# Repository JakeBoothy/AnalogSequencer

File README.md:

# SoundLabSequencer
A eurorack analog sequencer.

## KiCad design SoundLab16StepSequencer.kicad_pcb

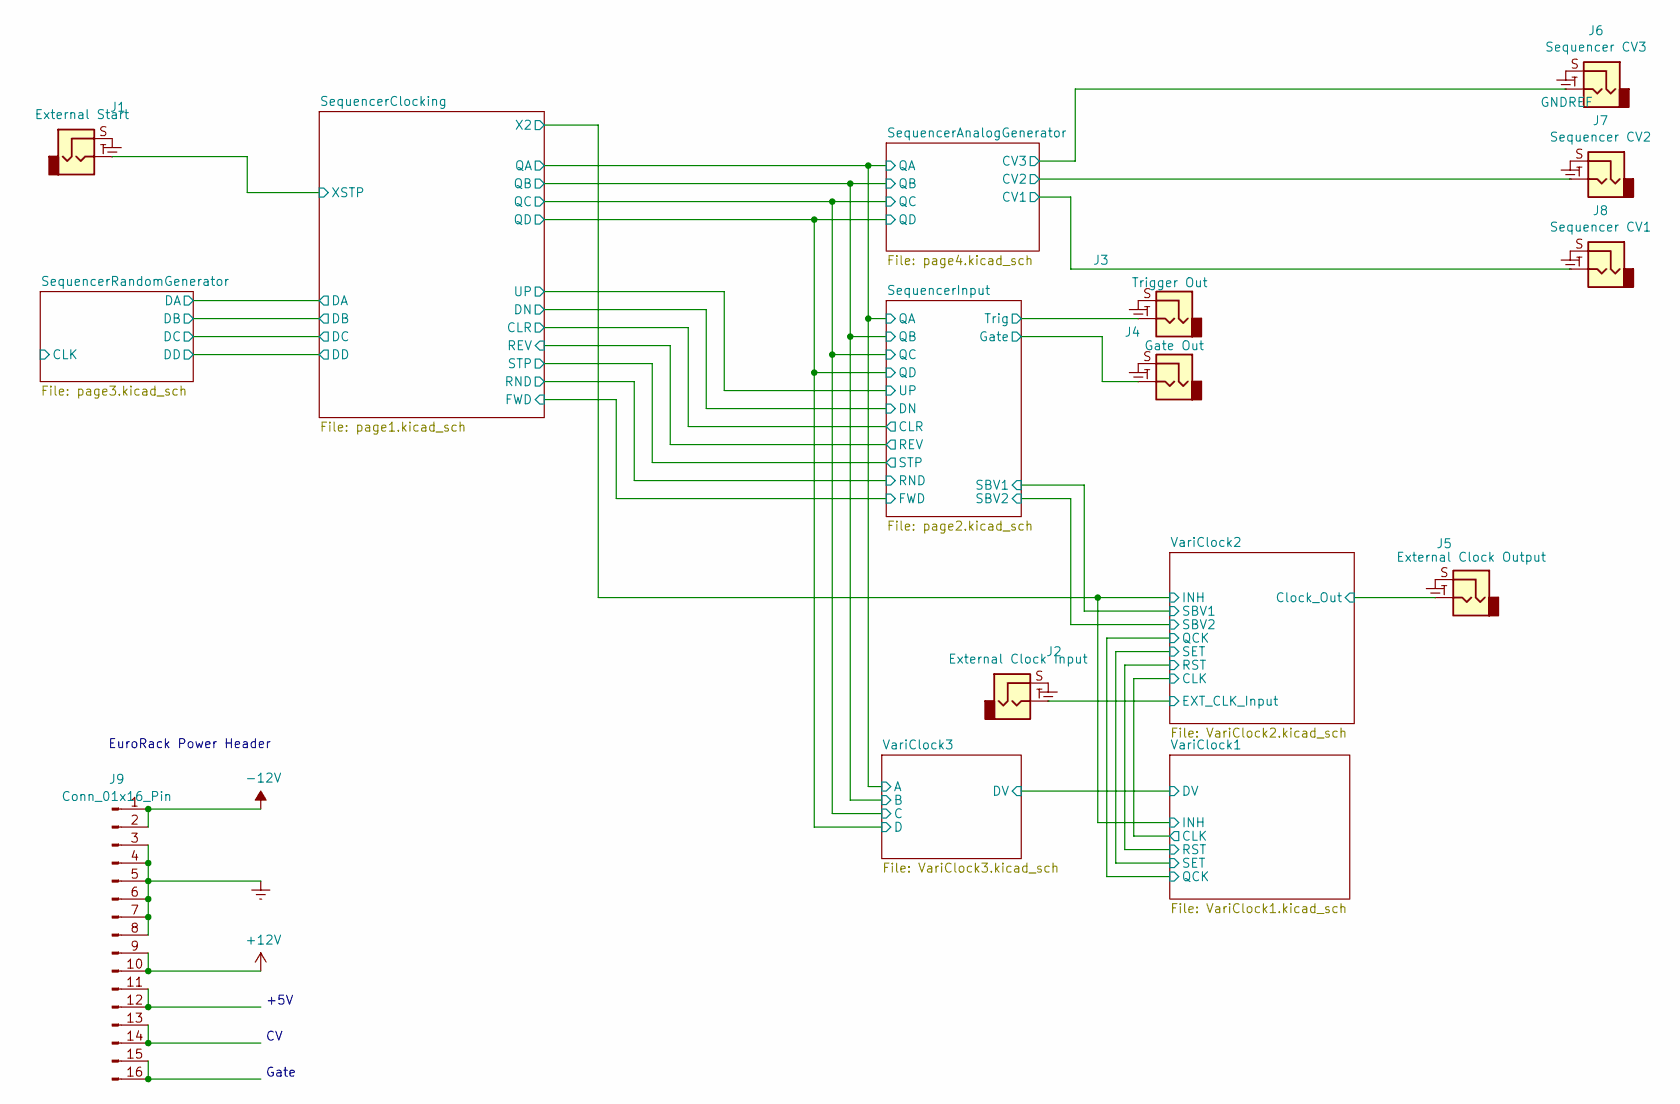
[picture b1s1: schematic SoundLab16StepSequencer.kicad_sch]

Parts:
J1: External Start; PJ-301
J2: External Clock Input; PJ-301
J3: Trigger Out; PJ-301
J4: Gate Out; PJ-301
J5: External Clock Output; PJ-301
J6: Sequencer CV3; PJ-301
J7: Sequencer CV2; PJ-301
J8: Sequencer CV1; PJ-301
J9: Conn_01x16_Pin; PinHeader_2x08_P2.54mm_Vertical

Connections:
+12V: J9.9, J9.10; also elsewhere on the board
-12V: J9.1, J9.2; also elsewhere on the board
/SequencerAnalogGenerator/CV1: J8.T; also elsewhere on the board
/SequencerAnalogGenerator/CV2: J7.T; also elsewhere on the board
/SequencerAnalogGenerator/CV3: J6.T; also elsewhere on the board
/SequencerClocking/XSTP: J1.T; also elsewhere on the board
/SequencerInput/Gate: J4.T; also elsewhere on the board
/SequencerInput/Trig: J3.T; also elsewhere on the board
/VariClock2/Clock_Out: J5.T; also elsewhere on the board
/VariClock2/EXT_CLK_Input: J2.T; also elsewhere on the board
GNDREF: J1.S, J2.S, J3.S, J4.S, J5.S, J6.S, J7.S, J8.S, J9.3, J9.4, J9.5, J9.6, J9.7, J9.8; also elsewhere on the board
unnamed: J9.11, J9.12
unnamed: J9.13, J9.14
unnamed: J9.15, J9.16

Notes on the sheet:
Gate
EuroRack Power Header
+5V

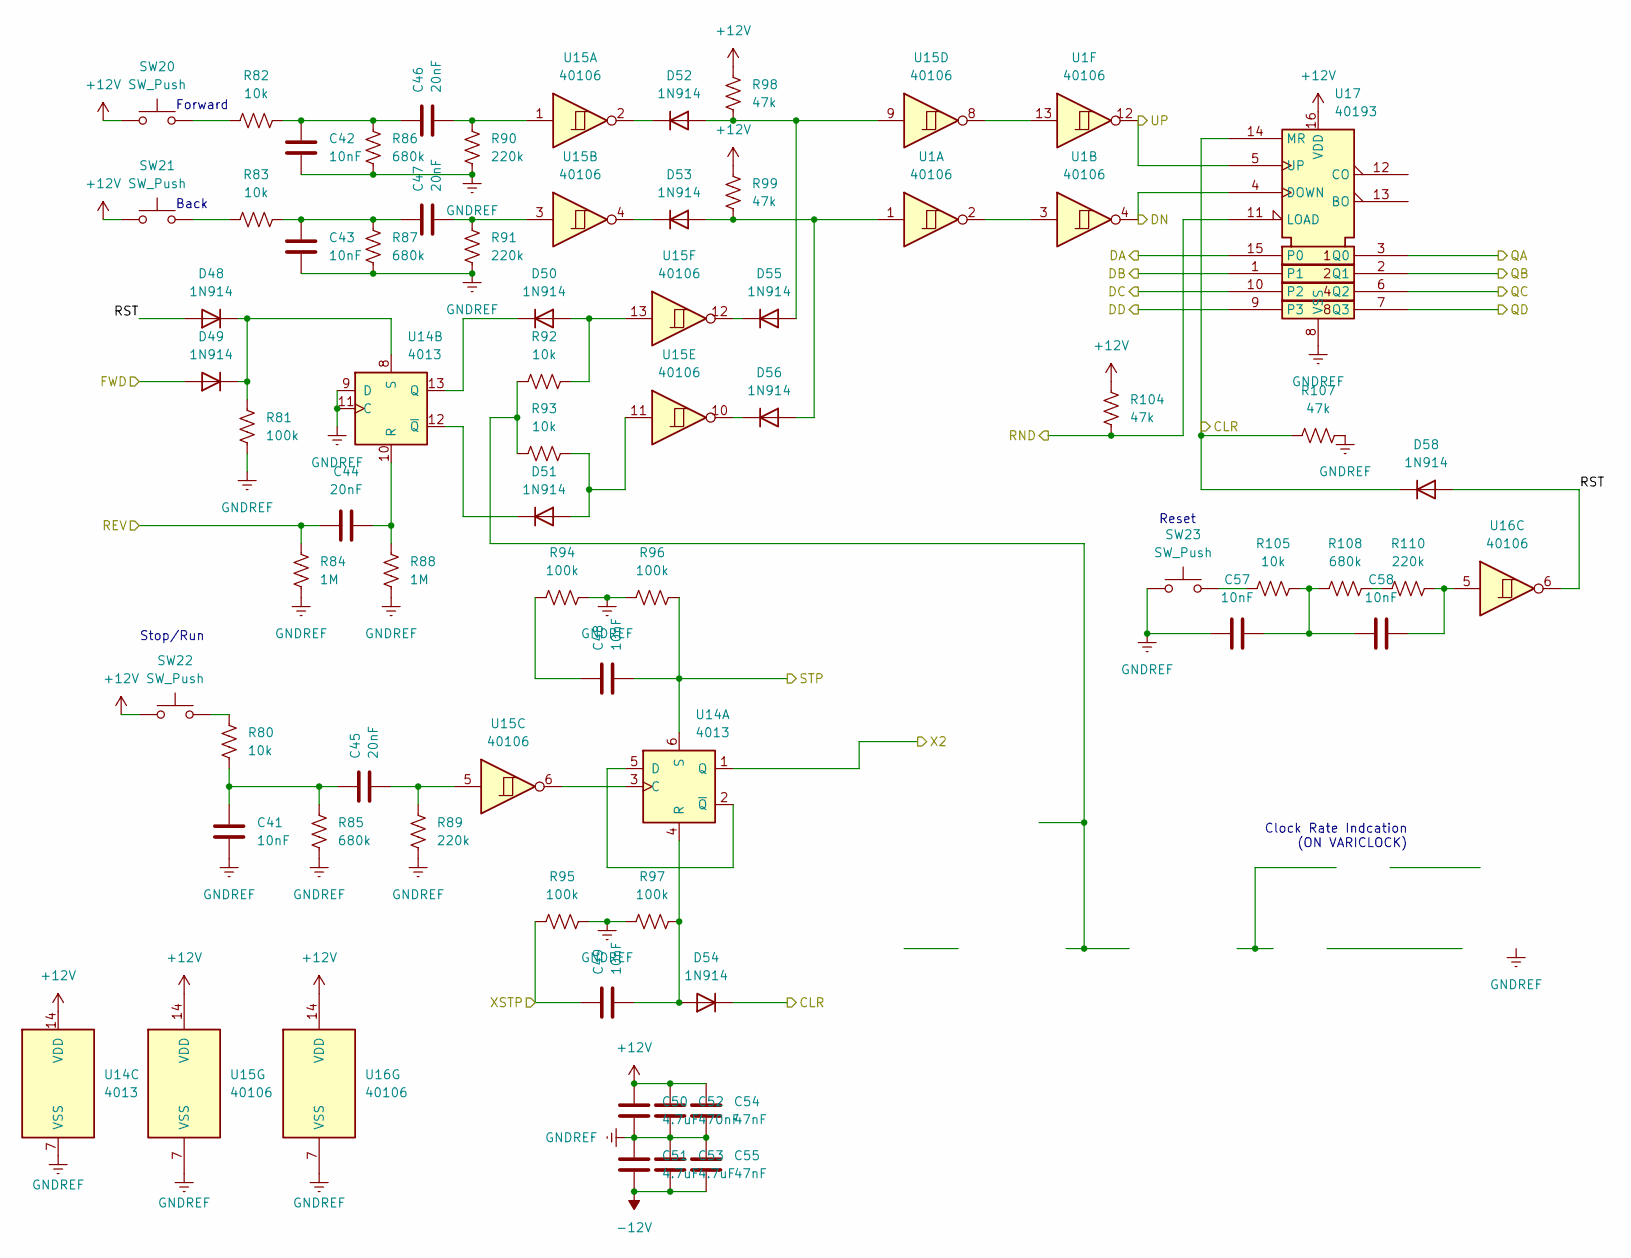
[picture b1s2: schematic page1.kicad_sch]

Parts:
C41, C42, C43, C48, C49, C57, C58: 10nF; C_0603_1608Metric
C44, C45, C46, C47: 20nF; C_0603_1608Metric
C50, C51, C53: 4.7uF; C_0805_2012Metric
C52: 470nF; C_0805_2012Metric
C54, C55: 47nF; C_0603_1608Metric
D48, D49, D50, D51, D52, D53, D54, D55, D56, D58: 1N914; D_SOD-323F
R80, R82, R83, R92, R93, R105: 10k; R_0603_1608Metric
R81, R94, R95, R96, R97: 100k; R_0603_1608Metric
R84, R88: 1M; R_0603_1608Metric
R85, R86, R87, R108: 680k; R_0603_1608Metric
R89, R90, R91, R110: 220k; R_0603_1608Metric
R98, R99, R104, R107: 47k; R_0603_1608Metric
SW20, SW21, SW22, SW23: SW_Push; SW_PUSH_6mm_H13mm
U1, U15, U16: 40106; SOIC-14_3.9x8.7mm_P1.27mm
U14: 4013; SOIC-14_3.9x8.7mm_P1.27mm
U17: 40193; SOIC-16W_5.3x10.2mm_P1.27mm

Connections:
+12V: C50.1, C52.1, C54.1, R98.1, R99.1, R104.2, SW20.1, SW21.1, SW22.1, U14.14 (VDD), U15.14 (VDD), U16.14 (VDD), U17.16 (VDD); also elsewhere on the board
-12V: C51.2, C53.2, C55.2; also elsewhere on the board
/SequencerAnalogGenerator/QA: U17.3 (Q0); also elsewhere on the board
/SequencerAnalogGenerator/QB: U17.2 (Q1); also elsewhere on the board
/SequencerAnalogGenerator/QC: U17.6 (Q2); also elsewhere on the board
/SequencerAnalogGenerator/QD: U17.7 (Q3); also elsewhere on the board
/SequencerClocking/CLR: D54.1 (K), D58.1 (K), R107.2, U17.14 (MR); also elsewhere on the board
/SequencerClocking/DA: U17.15 (P0); also elsewhere on the board
/SequencerClocking/DB: U17.1; also elsewhere on the board
/SequencerClocking/DC: U17.10 (P2); also elsewhere on the board
/SequencerClocking/DD: U17.9 (P3); also elsewhere on the board
/SequencerClocking/DN: U1.4, U17.4 (DOWN); also elsewhere on the board
/SequencerClocking/FWD: D49.2 (A); also elsewhere on the board
/SequencerClocking/REV: C44.2, R84.2; also elsewhere on the board
/SequencerClocking/RND: R104.1, U17.11 (LOAD); also elsewhere on the board
/SequencerClocking/RST: D48.2 (A), D58.2 (A), U16.6
/SequencerClocking/STP: C48.2, R96.2, U14.6 (S); also elsewhere on the board
/SequencerClocking/UP: U1.12, U17.5 (UP); also elsewhere on the board
/SequencerClocking/X2: U14.1 (Q); also elsewhere on the board
/SequencerClocking/XSTP: C49.1, R95.1; also elsewhere on the board
GNDREF: C41.2, C42.2, C43.2, C50.2, C51.1, C52.2, C53.1, C54.2, C55.1, C57.2, R81.1, R84.1, R85.1, R86.1, R87.1, R88.1, R89.1, R90.1, R91.1, R94.2, R95.2, R96.1, R97.1, R107.1, SW23.1, U14.7 (VSS), U14.9 (D), U14.11 (C), U15.7 (VSS), U16.7 (VSS), U17.8 (VSS); also elsewhere on the board
unnamed: C41.1, C45.1, R80.1, R85.2
unnamed: C42.1, C46.1, R82.2, R86.2
unnamed: C43.1, C47.1, R83.2, R87.2
unnamed: C45.2, R89.2, U15.5
unnamed: C46.2, R90.2, U15.1
unnamed: C47.2, R91.2, U15.3
unnamed: C48.1, R94.1
unnamed: C57.1, C58.2, R105.1, R108.2
unnamed: C58.1, R110.1, U16.5
unnamed: D48.1 (K), D49.1 (K), R81.2, U14.8 (S)
unnamed: D50.2 (A), R92.2, U15.13
unnamed: D50.1 (K), U14.13 (Q)
unnamed: D51.2 (A), R93.2, U15.11
unnamed: D51.1 (K), U14.12 (~Q)
unnamed: D52.2 (A), D55.2 (A), R98.2, U15.9
unnamed: D52.1 (K), U15.2
unnamed: D53.2 (A), D56.2 (A), R99.2, U1.1
unnamed: D53.1 (K), U15.4
unnamed: C49.2, D54.2 (A), R97.2, U14.4 (R)
unnamed: D55.1 (K), U15.12
unnamed: D56.1 (K), U15.10
unnamed: R80.2, SW22.2
unnamed: R82.1, SW20.2
unnamed: R83.1, SW21.2
unnamed: R92.1, R93.1
unnamed: R105.2, SW23.2
unnamed: R108.1, R110.2
unnamed: U1.2, U1.3
unnamed: U1.13, U15.8
unnamed: U14.3 (C), U15.6
unnamed: U14.2 (~Q), U14.5 (D)
unnamed: C44.1, R88.2, U14.10 (R)

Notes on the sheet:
Reset
Clock Rate Indcation (ON VARICLOCK)
Back
Stop/Run
Forward

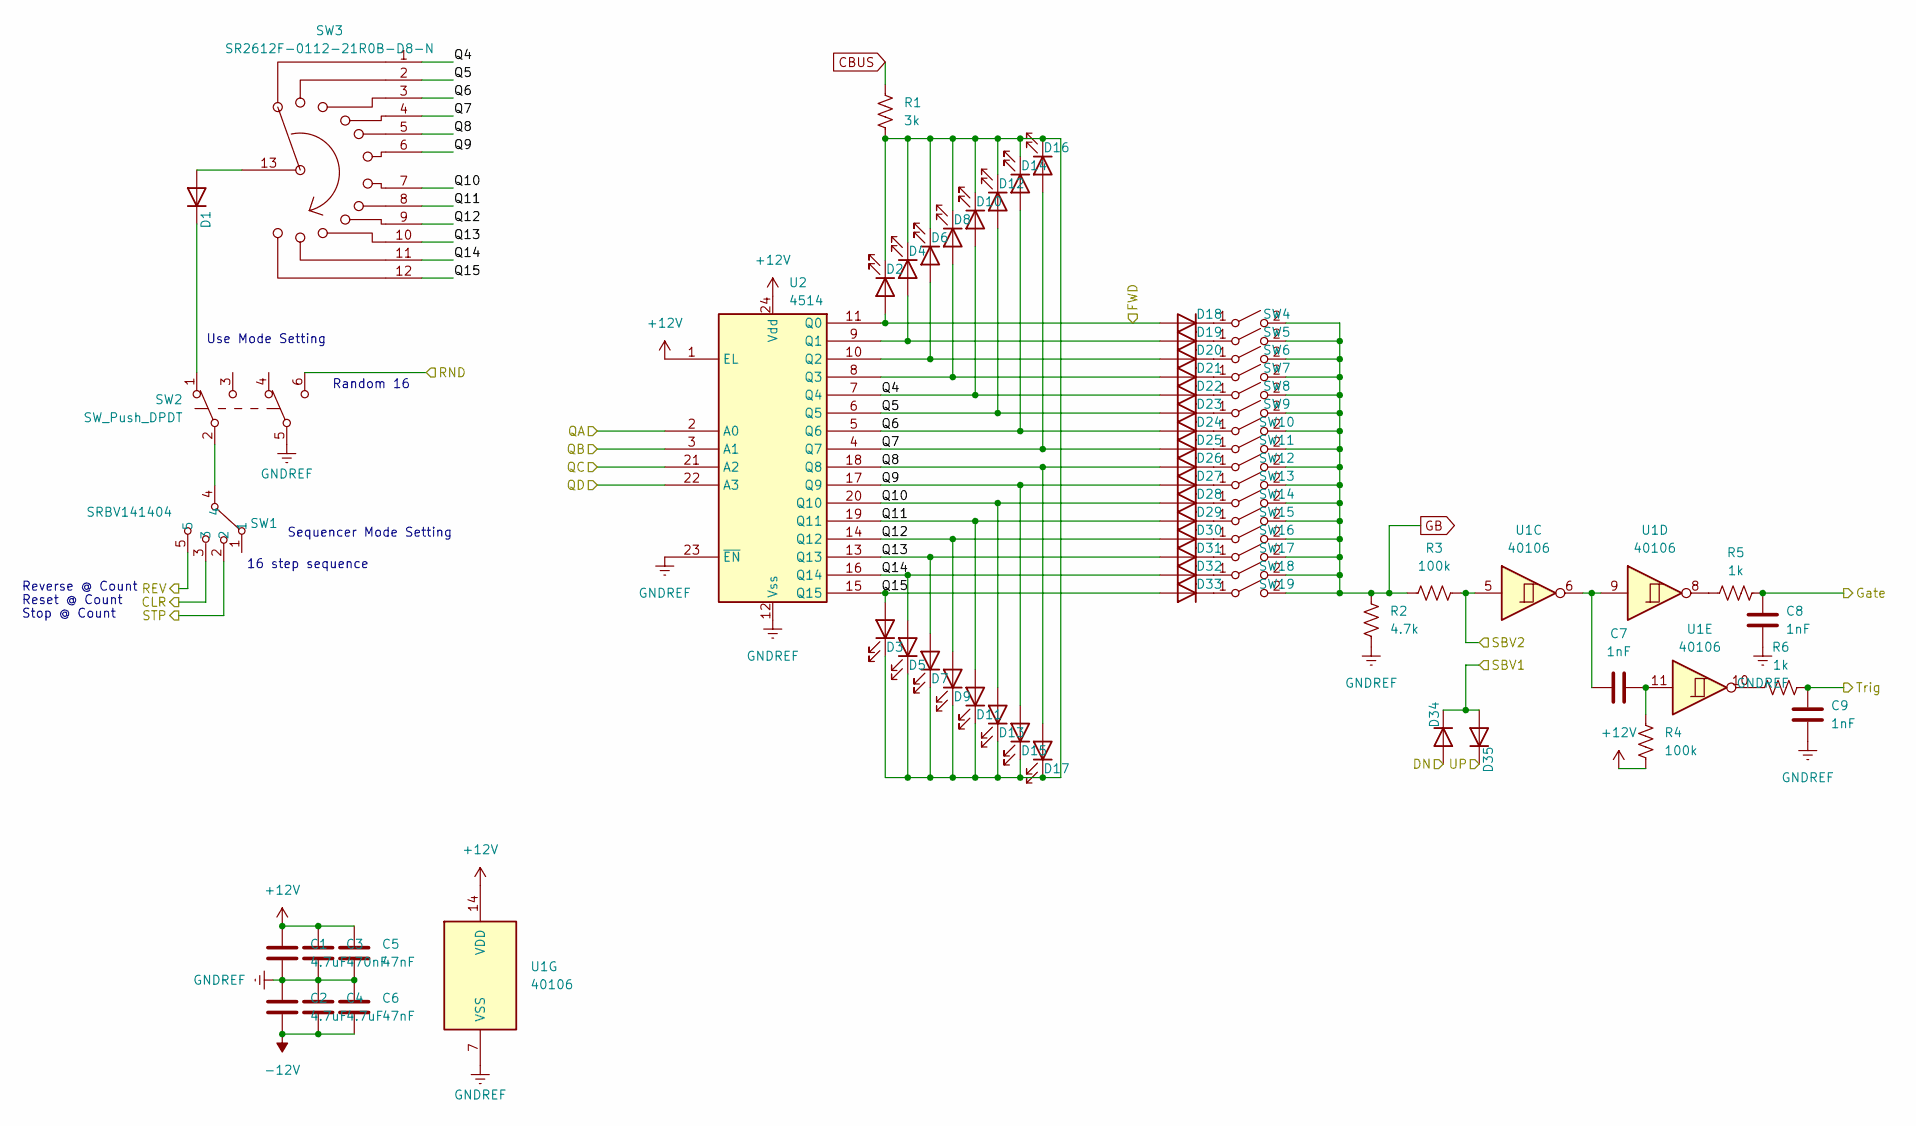
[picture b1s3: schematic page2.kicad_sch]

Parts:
C1, C2, C4: 4.7uF; C_0805_2012Metric
C3: 470nF; C_0805_2012Metric
C5, C6: 47nF; C_0603_1608Metric
C7, C8, C9: 1nF; C_0603_1608Metric
D1, D18, D19, D20, D21, D22, D23, D24, D25, D26, D27, D28, D29, D30, D31, D32, D33, D34, D35: 1N914; D_SOD-323F
D2, D3, D4, D5, D6, D7, D8, D9, D10, D11, D12, D13, D14, D15, D16, D17: LED; LED_D5.0mm
R1: 3k; R_0603_1608Metric
R2: 4.7k; R_0603_1608Metric
R3, R4: 100k; R_0603_1608Metric
R5, R6: 1k; R_0603_1608Metric
SW1: SRBV141404
SW2: SW_Push_DPDT; MTS-203-A1-T0
SW3: SR2612F-0112-21R0B-D8-N; SR2612F-0112
SW4, SW5, SW6, SW7, SW8, SW9, SW10, SW11, SW12, SW13, SW14, SW15, SW16, SW17, SW18, SW19: SW_SPST; MTS-103-A01-T0
U1: 40106; SOIC-14_3.9x8.7mm_P1.27mm
U2: 4514; SOIC-24W_7.5x15.4mm_P1.27mm

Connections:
+12V: C1.1, C3.1, C5.1, R4.1, U1.14 (VDD), U2.1 (EL), U2.24 (Vdd); also elsewhere on the board
-12V: C2.2, C4.2, C6.2; also elsewhere on the board
/SequencerAnalogGenerator/QA: U2.2 (A0); also elsewhere on the board
/SequencerAnalogGenerator/QB: U2.3 (A1); also elsewhere on the board
/SequencerAnalogGenerator/QC: U2.21 (A2); also elsewhere on the board
/SequencerAnalogGenerator/QD: U2.22 (A3); also elsewhere on the board
/SequencerClocking/CLR: SW1.3; also elsewhere on the board
/SequencerClocking/DN: D34.2 (A); also elsewhere on the board
/SequencerClocking/FWD: D2.2 (A), D18.2 (A), U2.11 (Q0); also elsewhere on the board
/SequencerClocking/REV: SW1.5; also elsewhere on the board
/SequencerClocking/RND: SW2.6 (C); also elsewhere on the board
/SequencerClocking/STP: SW1.2; also elsewhere on the board
/SequencerClocking/UP: D35.1 (K); also elsewhere on the board
/SequencerInput/Gate: C8.2, R5.2; also elsewhere on the board
/SequencerInput/Q4: D10.2 (A), D22.2 (A), SW3.1, U2.7 (Q4)
/SequencerInput/Q5: D12.2 (A), D23.2 (A), SW3.2, U2.6 (Q5)
/SequencerInput/Q6: D14.2 (A), D24.2 (A), SW3.3, U2.5 (Q6)
/SequencerInput/Q7: D16.2 (A), D25.2 (A), SW3.4, U2.4 (Q7)
/SequencerInput/Q8: D17.2 (A), D26.2 (A), SW3.5, U2.18 (Q8)
/SequencerInput/Q9: D15.2 (A), D27.2 (A), SW3.6, U2.17 (Q9)
/SequencerInput/Q10: D13.2 (A), D28.2 (A), SW3.7, U2.20 (Q10)
/SequencerInput/Q11: D11.2 (A), D29.2 (A), SW3.8, U2.19 (Q11)
/SequencerInput/Q12: D9.2 (A), D30.2 (A), SW3.9, U2.14 (Q12)
/SequencerInput/Q13: D7.2 (A), D31.2 (A), SW3.10, U2.13 (Q13)
/SequencerInput/Q14: D5.2 (A), D32.2 (A), SW3.11, U2.16 (Q14)
/SequencerInput/Q15: D3.2 (A), D33.2 (A), SW3.12, U2.15 (Q15)
/SequencerInput/SBV1: D34.1 (K), D35.2 (A); also elsewhere on the board
/SequencerInput/SBV2: R3.2, U1.5; also elsewhere on the board
/SequencerInput/Trig: C9.2, R6.2; also elsewhere on the board
CBUS: R1.1
GB: R2.1, R3.1, SW4.2 (B), SW5.2 (B), SW6.2 (B), SW7.2 (B), SW8.2 (B), SW9.2 (B), SW10.2 (B), SW11.2 (B), SW12.2 (B), SW13.2 (B), SW14.2 (B), SW15.2 (B), SW16.2 (B), SW17.2 (B), SW18.2 (B), SW19.2 (B)
GNDREF: C1.2, C2.1, C3.2, C4.1, C5.2, C6.1, C8.1, C9.1, R2.2, SW2.5 (B), U1.7 (VSS), U2.12 (Vss), U2.23 (~EN); also elsewhere on the board
unnamed: C7.1, U1.6, U1.9
unnamed: C7.2, R4.2, U1.11
unnamed: D1.2 (A), SW3.13
unnamed: D1.1 (K), SW2.1 (A)
unnamed: D2.1 (K), D3.1 (K), D4.1 (K), D5.1 (K), D6.1 (K), D7.1 (K), D8.1 (K), D9.1 (K), D10.1 (K), D11.1 (K), D12.1 (K), D13.1 (K), D14.1 (K), D15.1 (K), D16.1 (K), D17.1 (K), R1.2
unnamed: D18.1 (K), SW4.1 (A)
unnamed: D4.2 (A), D19.2 (A), U2.9 (Q1)
unnamed: D19.1 (K), SW5.1 (A)
unnamed: D6.2 (A), D20.2 (A), U2.10 (Q2)
unnamed: D20.1 (K), SW6.1 (A)
unnamed: D8.2 (A), D21.2 (A), U2.8 (Q3)
unnamed: D21.1 (K), SW7.1 (A)
unnamed: D22.1 (K), SW8.1 (A)
unnamed: D23.1 (K), SW9.1 (A)
unnamed: D24.1 (K), SW10.1 (A)
unnamed: D25.1 (K), SW11.1 (A)
unnamed: D26.1 (K), SW12.1 (A)
unnamed: D27.1 (K), SW13.1 (A)
unnamed: D28.1 (K), SW14.1 (A)
unnamed: D29.1 (K), SW15.1 (A)
unnamed: D30.1 (K), SW16.1 (A)
unnamed: D31.1 (K), SW17.1 (A)
unnamed: D32.1 (K), SW18.1 (A)
unnamed: D33.1 (K), SW19.1 (A)
unnamed: R5.1, U1.8
unnamed: R6.1, U1.10
unnamed: SW1.4, SW2.2 (B)

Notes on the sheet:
Sequencer Mode Setting
Random 16
Stop @ Count
Reset @ Count
Reverse @ Count
16 step sequence
Use Mode Setting

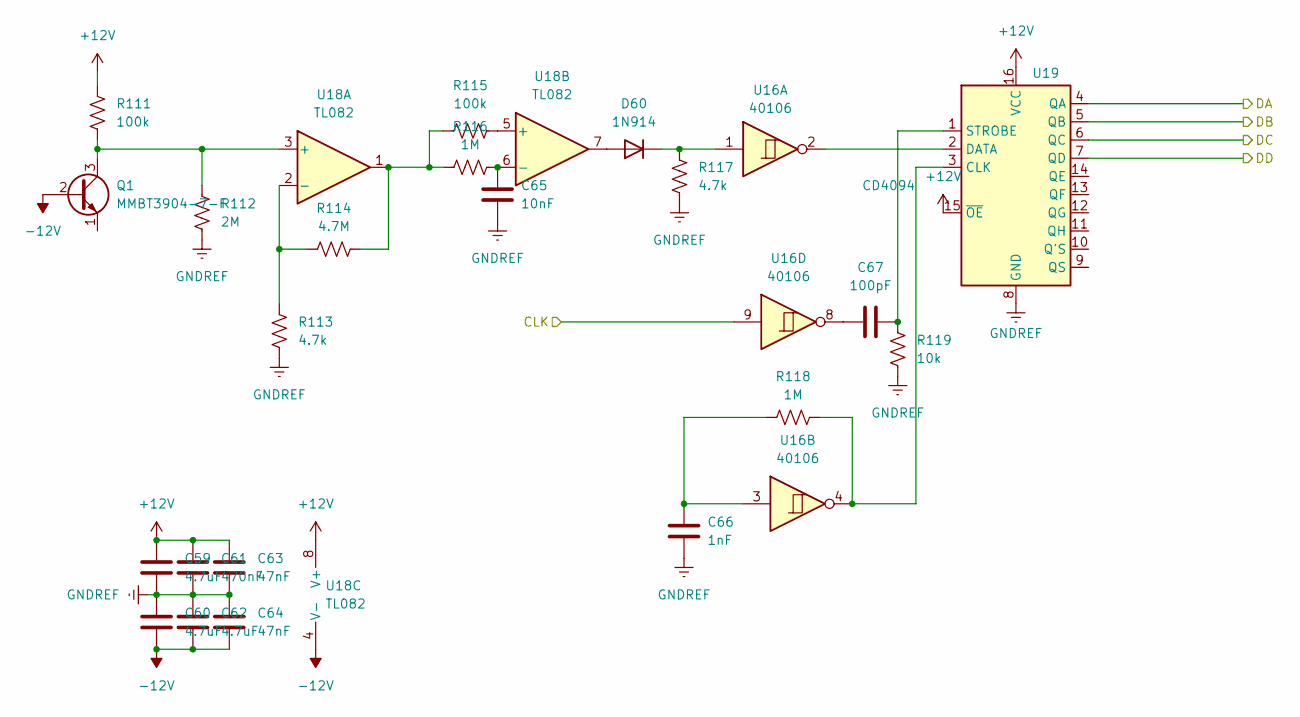
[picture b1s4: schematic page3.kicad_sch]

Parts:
C59, C60, C62: 4.7uF; C_0805_2012Metric
C61: 470nF; C_0805_2012Metric
C63, C64: 47nF; C_0603_1608Metric
C65: 10nF; C_0603_1608Metric
C66: 1nF; C_0603_1608Metric
C67: 100pF; C_0603_1608Metric
D60: 1N914; D_SOD-323F
Q1: MMBT3904-7-F; SOT-23-3
R111, R115: 100k; R_0603_1608Metric
R112: 2M; R_0603_1608Metric
R113, R117: 4.7k; R_0603_1608Metric
R114: 4.7M; R_0603_1608Metric
R116, R118: 1M; R_0603_1608Metric
R119: 10k; R_0603_1608Metric
U16: 40106; SOIC-14_3.9x8.7mm_P1.27mm
U18: TL082; SOIC-8_3.9x4.9mm_P1.27mm
U19: CD4094; SOP-16_3.9x9.9mm_P1.27mm

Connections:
+12V: C59.1, C61.1, C63.1, R111.2, U18.8 (V+), U19.15 (~OE), U19.16 (VCC); also elsewhere on the board
-12V: C60.2, C62.2, C64.2, Q1.2 (B), U18.4 (V-); also elsewhere on the board
/SequencerClocking/DA: U19.4 (QA); also elsewhere on the board
/SequencerClocking/DB: U19.5 (QB); also elsewhere on the board
/SequencerClocking/DC: U19.6 (QC); also elsewhere on the board
/SequencerClocking/DD: U19.7 (QD); also elsewhere on the board
/SequencerRandomGenerator/CLK: U16.9
GNDREF: C59.2, C60.1, C61.2, C62.1, C63.2, C64.1, C65.1, C66.1, R112.1, R113.1, R117.1, R119.1, U19.8 (GND); also elsewhere on the board
unnamed: C66.2, R118.2, U16.3
unnamed: C67.2, U16.8
unnamed: D60.2 (A), U18.7
unnamed: D60.1 (K), R117.2, U16.1
unnamed: Q1.3 (C), R111.1, R112.2, U18.3 (+)
unnamed: R114.1, R115.2, R116.2, U18.1
unnamed: R113.2, R114.2, U18.2 (-)
unnamed: R115.1, U18.5 (+)
unnamed: C65.2, R116.1, U18.6 (-)
unnamed: R118.1, U16.4, U19.3 (CLK)
unnamed: U16.2, U19.2 (DATA)
unnamed: C67.1, R119.2, U19.1 (STROBE)

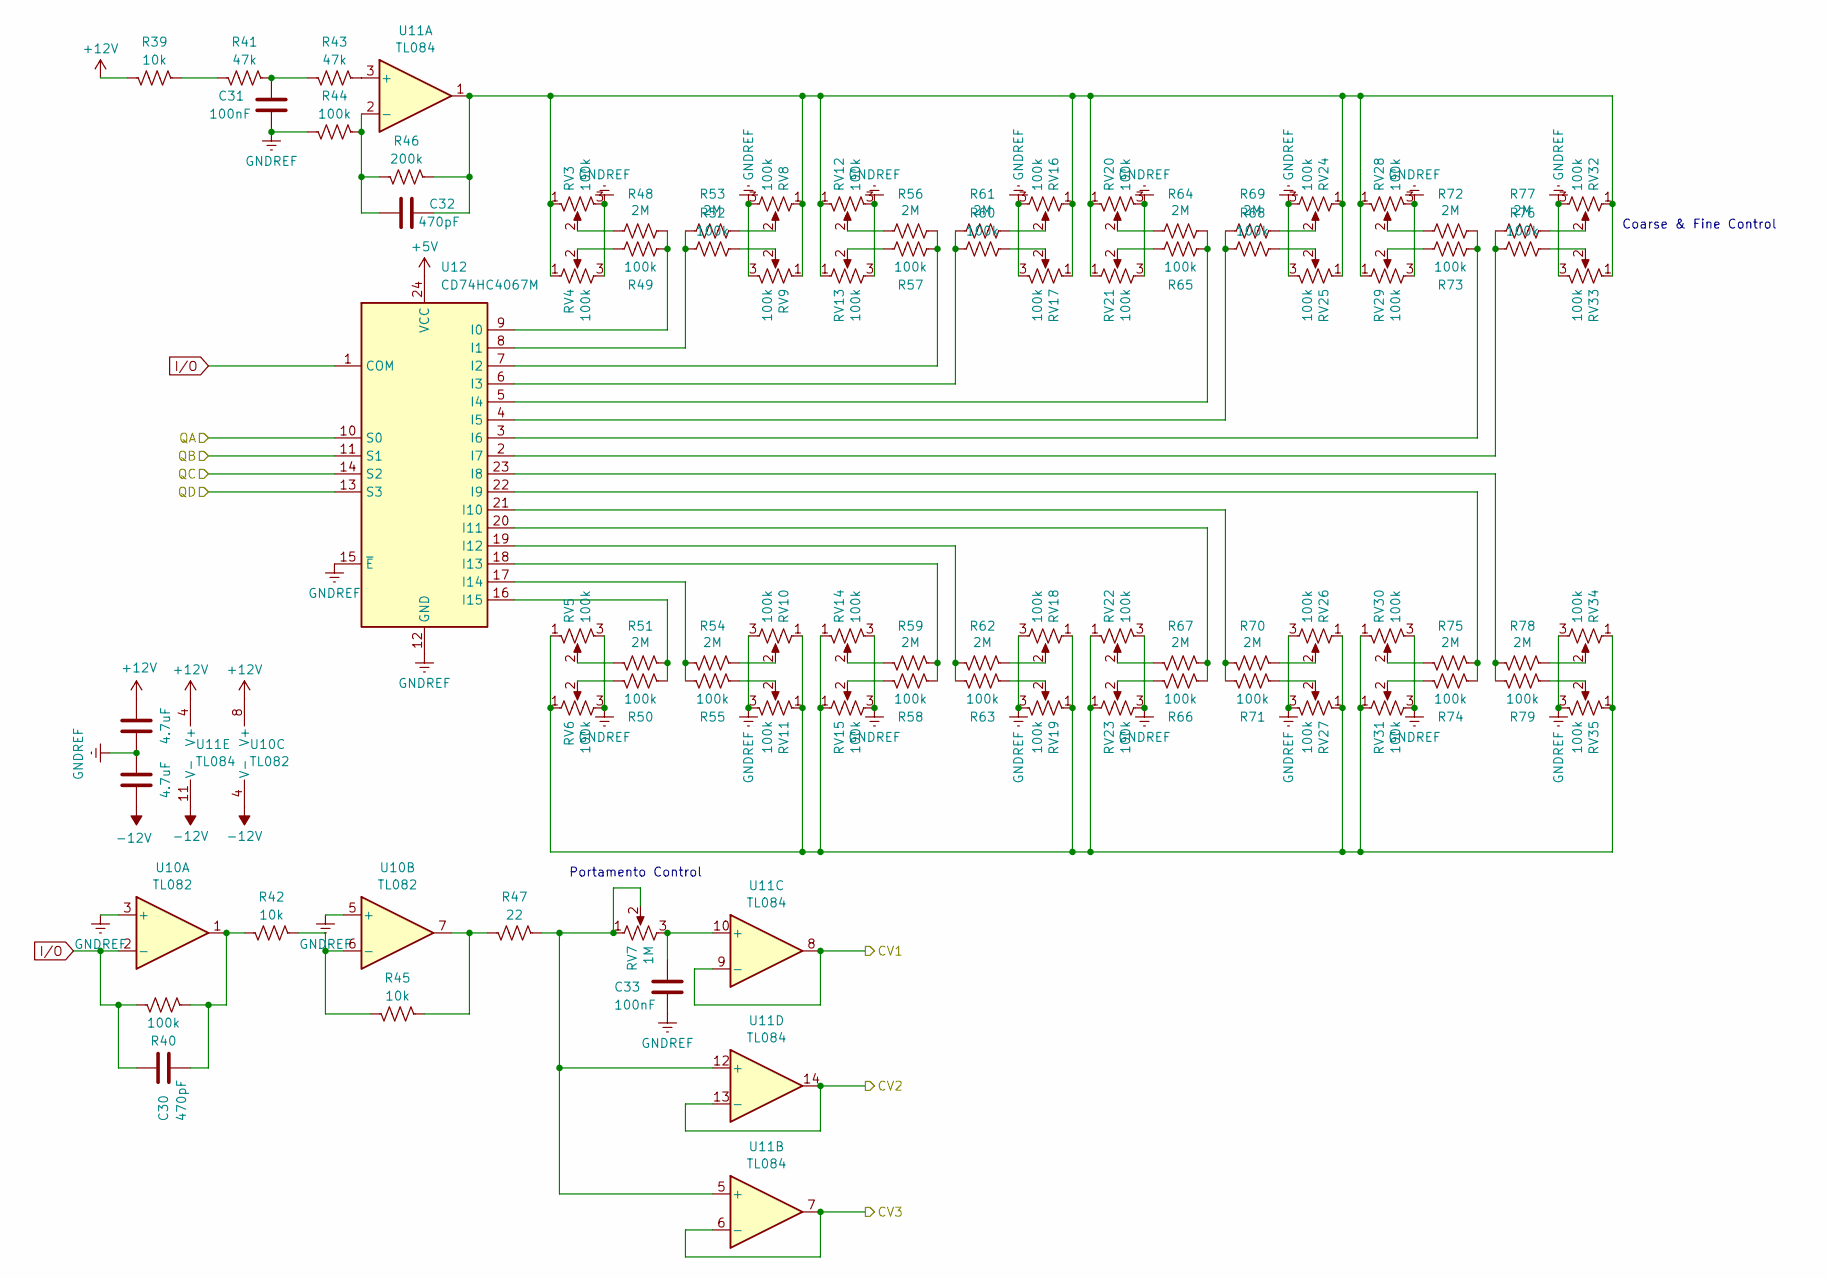
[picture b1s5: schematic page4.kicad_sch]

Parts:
C28, C29: 4.7uF; C_0805_2012Metric
C30, C32: 470pF; C_0603_1608Metric
C31, C33: 100nF; C_0603_1608Metric
R39, R42, R45: 10k; R_0603_1608Metric
R40, R44, R49, R50, R52, R55, R57, R58, R60, R63, R65, R66, R68, R71, R73, R74, R76, R79: 100k; R_0603_1608Metric
R41, R43: 47k; R_0603_1608Metric
R46: 200k; R_0603_1608Metric
R47: 22; R_0603_1608Metric
R48, R51, R53, R54, R56, R59, R61, R62, R64, R67, R69, R70, R72, R75, R77, R78: 2M; R_0603_1608Metric
RV3, RV4, RV5, RV6, RV8, RV9, RV10, RV11, RV12, RV13, RV14, RV15, RV16, RV17, RV18, RV19, RV20, RV21, RV22, RV23, RV24, RV25, RV26, RV27, RV28, RV29, RV30, RV31, RV32, RV33, RV34, RV35: 100k; Potentiometer_Alps_RK09K_Single_Vertical
RV7: 1M; Potentiometer_Alps_RK09K_Single_Vertical
U10: TL082; SOIC-8_3.9x4.9mm_P1.27mm
U11: TL084; SO-14_3.9x8.65mm_P1.27mm
U12: CD74HC4067M; SOIC-24W_7.5x15.4mm_P1.27mm

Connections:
+5V: U12.24 (VCC)
+12V: C28.2, R39.2, U10.8 (V+), U11.4 (V+); also elsewhere on the board
-12V: C29.1, U10.4 (V-), U11.11 (V-); also elsewhere on the board
/SequencerAnalogGenerator/CV1: U11.8, U11.9 (-); also elsewhere on the board
/SequencerAnalogGenerator/CV2: U11.13 (-), U11.14; also elsewhere on the board
/SequencerAnalogGenerator/CV3: U11.6 (-), U11.7; also elsewhere on the board
/SequencerAnalogGenerator/QA: U12.10 (S0); also elsewhere on the board
/SequencerAnalogGenerator/QB: U12.11 (S1); also elsewhere on the board
/SequencerAnalogGenerator/QC: U12.14 (S2); also elsewhere on the board
/SequencerAnalogGenerator/QD: U12.13 (S3); also elsewhere on the board
GNDREF: C28.1, C29.2, C31.2, C33.2, R44.2, RV3.3, RV4.3, RV5.3, RV6.3, RV8.3, RV9.3, RV10.3, RV11.3, RV12.3, RV13.3, RV14.3, RV15.3, RV16.3, RV17.3, RV18.3, RV19.3, RV20.3, RV21.3, RV22.3, RV23.3, RV24.3, RV25.3, RV26.3, RV27.3, RV28.3, RV29.3, RV30.3, RV31.3, RV32.3, RV33.3, RV34.3, RV35.3, U10.3 (+), U10.5 (+), U12.12 (GND), U12.15 (~E); also elsewhere on the board
I/O: C30.1, R40.1, U10.2 (-), U12.1 (COM)
unnamed: C30.2, R40.2, R42.2, U10.1
unnamed: C31.1, R41.1, R43.2
unnamed: C32.2, R46.1, RV3.1, RV4.1, RV8.1, RV9.1, RV12.1, RV13.1, RV16.1, RV17.1, RV20.1, RV21.1, RV24.1, RV25.1, RV28.1, RV29.1, RV32.1, RV33.1, U11.1
unnamed: R39.1, R41.2
unnamed: R45.1, R47.2, U10.7
unnamed: R48.2, RV3.2
unnamed: R49.2, RV4.2
unnamed: R50.1, RV6.2
unnamed: R51.1, RV5.2
unnamed: R52.2, RV9.2
unnamed: R53.1, RV8.2
unnamed: R54.2, RV10.2
unnamed: R55.2, RV11.2
unnamed: R56.2, RV12.2
unnamed: R57.2, RV13.2
unnamed: R58.1, RV15.2
unnamed: R59.1, RV14.2
unnamed: R60.2, RV17.2
unnamed: R61.1, RV16.2
unnamed: R62.2, RV18.2
unnamed: R63.2, RV19.2
unnamed: R64.2, RV20.2
unnamed: R65.2, RV21.2
unnamed: R66.1, RV23.2
unnamed: R67.1, RV22.2
unnamed: R68.2, RV25.2
unnamed: R69.1, RV24.2
unnamed: R70.2, RV26.2
unnamed: R71.2, RV27.2
unnamed: R72.2, RV28.2
unnamed: R73.2, RV29.2
unnamed: R74.1, RV31.2
unnamed: R75.1, RV30.2
unnamed: R76.2, RV33.2
unnamed: R77.1, RV32.2
unnamed: R78.2, RV34.2
unnamed: R79.2, RV35.2
unnamed: RV5.1, RV6.1, RV10.1, RV11.1, RV14.1, RV15.1, RV18.1, RV19.1, RV22.1, RV23.1, RV26.1, RV27.1, RV30.1, RV31.1, RV34.1, RV35.1
unnamed: R42.1, R45.2, U10.6 (-)
unnamed: R43.1, U11.3 (+)
unnamed: C32.1, R44.1, R46.2, U11.2 (-)
unnamed: R47.1, RV7.1, RV7.2, U11.5 (+), U11.12 (+)
unnamed: C33.1, RV7.3, U11.10 (+)
unnamed: R48.1, R49.1, U12.9 (I0)
unnamed: R52.1, R53.2, U12.8 (I1)
unnamed: R56.1, R57.1, U12.7 (I2)
unnamed: R60.1, R61.2, U12.6 (I3)
unnamed: R64.1, R65.1, U12.5 (I4)
unnamed: R68.1, R69.2, U12.4 (I5)
unnamed: R72.1, R73.1, U12.3 (I6)
unnamed: R76.1, R77.2, U12.2 (I7)
unnamed: R78.1, R79.1, U12.23 (I8)
unnamed: R74.2, R75.2, U12.22 (I9)
unnamed: R70.1, R71.1, U12.21 (I10)
unnamed: R66.2, R67.2, U12.20 (I11)
unnamed: R62.1, R63.1, U12.19 (I12)
unnamed: R58.2, R59.2, U12.18 (I13)
unnamed: R54.1, R55.1, U12.17 (I14)
unnamed: R50.2, R51.2, U12.16 (I15)

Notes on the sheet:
Coarse & Fine Control
Portamento Control

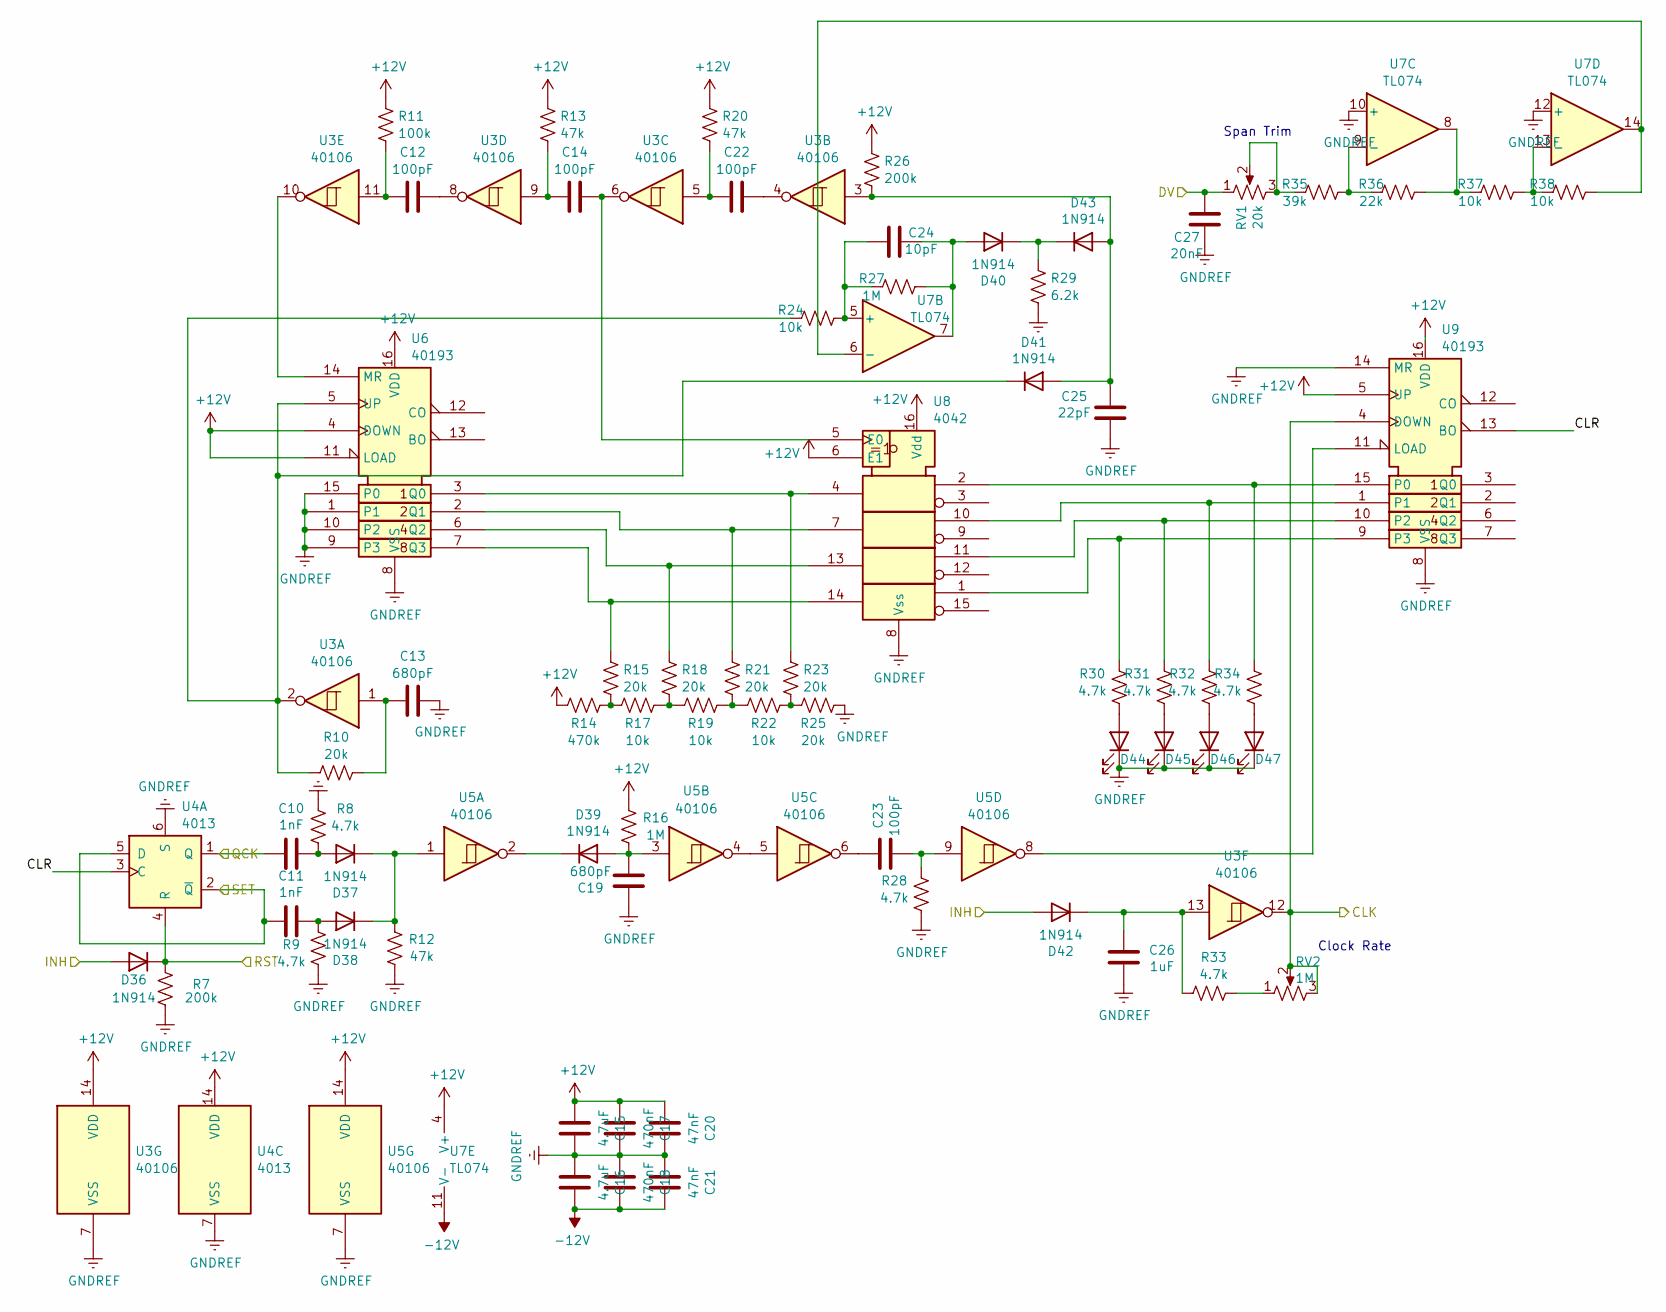
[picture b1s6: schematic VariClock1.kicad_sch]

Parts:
C10, C11: 1nF; C_0603_1608Metric
C12, C14, C22, C23: 100pF; C_0603_1608Metric
C13, C19: 680pF; C_0603_1608Metric
C15, C16: 4.7uF; C_0805_2012Metric
C17, C18: 470nF; C_0805_2012Metric
C20, C21: 47nF; C_0603_1608Metric
C24: 10pF; C_0603_1608Metric
C25: 22pF; C_0603_1608Metric
C26: 1uF; C_0805_2012Metric
C27: 20nF; C_0603_1608Metric
D36, D37, D38, D39, D40, D41, D42, D43: 1N914; D_SOD-323F
D44, D45, D46, D47: LED; LED_D5.0mm
R7, R26: 200k; R_0603_1608Metric
R8, R9, R28, R30, R31, R32, R33, R34: 4.7k; R_0603_1608Metric
R10, R15, R18, R21, R23, R25: 20k; R_0603_1608Metric
R11: 100k; R_0603_1608Metric
R12, R13, R20: 47k; R_0603_1608Metric
R14: 470k; R_0603_1608Metric
R16, R27: 1M; R_0603_1608Metric
R17, R19, R22, R24, R37, R38: 10k; R_0603_1608Metric
R29: 6.2k; R_0603_1608Metric
R35: 39k; R_0603_1608Metric
R36: 22k; R_0603_1608Metric
RV1: 20k; Potentiometer_Bourns_TC33X_Vertical
RV2: 1M; Potentiometer_Alps_RK09K_Single_Vertical
U3, U5: 40106; SOIC-14_3.9x8.7mm_P1.27mm
U4: 4013; SOIC-14_3.9x8.7mm_P1.27mm
U6, U9: 40193; SOIC-16W_5.3x10.2mm_P1.27mm
U7: TL074; SO-14_3.9x8.65mm_P1.27mm
U8: 4042; SOP-16_3.9x9.9mm_P1.27mm

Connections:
+12V: C15.2, C17.2, C20.2, R11.1, R13.1, R14.2, R16.1, R20.1, R26.1, U3.14 (VDD), U4.14 (VDD), U5.14 (VDD), U6.4 (DOWN), U6.11 (LOAD), U6.16 (VDD), U7.4 (V+), U8.6 (E1), U8.16 (Vdd), U9.5 (UP), U9.16 (VDD); also elsewhere on the board
-12V: C16.1, C18.1, C21.1, U7.11 (V-); also elsewhere on the board
/SequencerClocking/X2: D36.2 (A), D42.2 (A); also elsewhere on the board
/VariClock1/CLK: RV2.2, RV2.3, U3.12, U9.4 (DOWN); also elsewhere on the board
/VariClock1/CLR: U4.3 (C), U9.13 (BO)
/VariClock1/DV: C27.1, RV1.1; also elsewhere on the board
/VariClock1/QCK: C10.2, U4.1 (Q); also elsewhere on the board
/VariClock1/RST: D36.1 (K), R7.1, U4.4 (R); also elsewhere on the board
/VariClock1/SET: C11.2, U4.2 (~Q), U4.5 (D); also elsewhere on the board
GNDREF: C13.2, C15.1, C16.2, C17.1, C18.2, C19.2, C20.1, C21.2, C25.1, C26.1, C27.2, D44.1 (K), D45.1 (K), D46.1 (K), D47.1 (K), R7.2, R8.1, R9.2, R12.2, R25.1, R28.1, R29.1, U3.7 (VSS), U4.6 (S), U4.7 (VSS), U5.7 (VSS), U6.1, U6.8 (VSS), U6.9 (P3), U6.10 (P2), U6.15 (P0), U7.10 (+), U7.12 (+), U8.8 (Vss), U9.8 (VSS), U9.14 (MR); also elsewhere on the board
unnamed: C12.1, R11.2, U3.11
unnamed: C12.2, U3.8
unnamed: C13.1, R10.2, U3.1
unnamed: C14.1, R13.2, U3.9
unnamed: C22.1, R20.2, U3.5
unnamed: C22.2, U3.4
unnamed: C23.1, R28.2, U5.9
unnamed: C23.2, U5.6
unnamed: C10.1, D37.2 (A), R8.2
unnamed: D37.1 (K), D38.1 (K), R12.1, U5.1
unnamed: C11.1, D38.2 (A), R9.1
unnamed: C19.1, D39.2 (A), R16.2, U5.3
unnamed: D39.1 (K), U5.2
unnamed: C24.2, D40.2 (A), R27.1, U7.7
unnamed: D40.1 (K), D43.1 (K), R29.2
unnamed: C25.2, D41.2 (A), D43.2 (A), R26.2, U3.3
unnamed: D41.1 (K), R10.1, R24.2, U3.2, U6.5 (UP)
unnamed: C26.2, D42.1 (K), R33.1, U3.13
unnamed: D44.2 (A), R30.1
unnamed: D45.2 (A), R31.1
unnamed: D46.2 (A), R32.1
unnamed: D47.2 (A), R34.1
unnamed: R14.1, R15.1, R17.2
unnamed: R17.1, R18.1, R19.2
unnamed: R19.1, R21.1, R22.2
unnamed: R22.1, R23.1, R25.2
unnamed: R33.2, RV2.1
unnamed: R35.2, RV1.2, RV1.3
unnamed: R36.1, R37.2, U7.8
unnamed: U5.4, U5.5
unnamed: U3.10, U6.14 (MR)
unnamed: R23.2, U6.3 (Q0), U8.4
unnamed: R21.2, U6.2 (Q1), U8.7
unnamed: R18.2, U6.6 (Q2), U8.13
unnamed: R15.2, U6.7 (Q3), U8.14
unnamed: C24.1, R24.1, R27.2, U7.5 (+)
unnamed: R38.1, U7.6 (-), U7.14
unnamed: R35.1, R36.2, U7.9 (-)
unnamed: R37.1, R38.2, U7.13 (-)
unnamed: C14.2, U3.6, U8.5 (E0)
unnamed: U5.8, U9.11 (LOAD)
unnamed: R34.2, U8.2, U9.15 (P0)
unnamed: R32.2, U8.10, U9.1
unnamed: R31.2, U8.11, U9.10 (P2)
unnamed: R30.2, U8.1, U9.9 (P3)

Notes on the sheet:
Span Trim
Clock Rate
